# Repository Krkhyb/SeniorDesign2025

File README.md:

**SPE3D Humidity Sensor Repository**

This repository is for a senior design project for University of Science and Technology. Utilizing a HS3003, Rassberry Pi 5, and an LCD we are gathering humidity data on a SPEE3D machine on campus, recording data in a database, and allowing users to output specific data to a csv file for easy export.

Files included here: Gerber of both main PCB and sensor PCB, and schematics.

**Contributers:**

Evan Newcorn - Mechanical Design and PCB Design

Nathan Schoenberg - Housing and Software Implementation

Johnny Leech - Mechanical Design and Reporting

Kyle Kruel - Software Developer and Implementation

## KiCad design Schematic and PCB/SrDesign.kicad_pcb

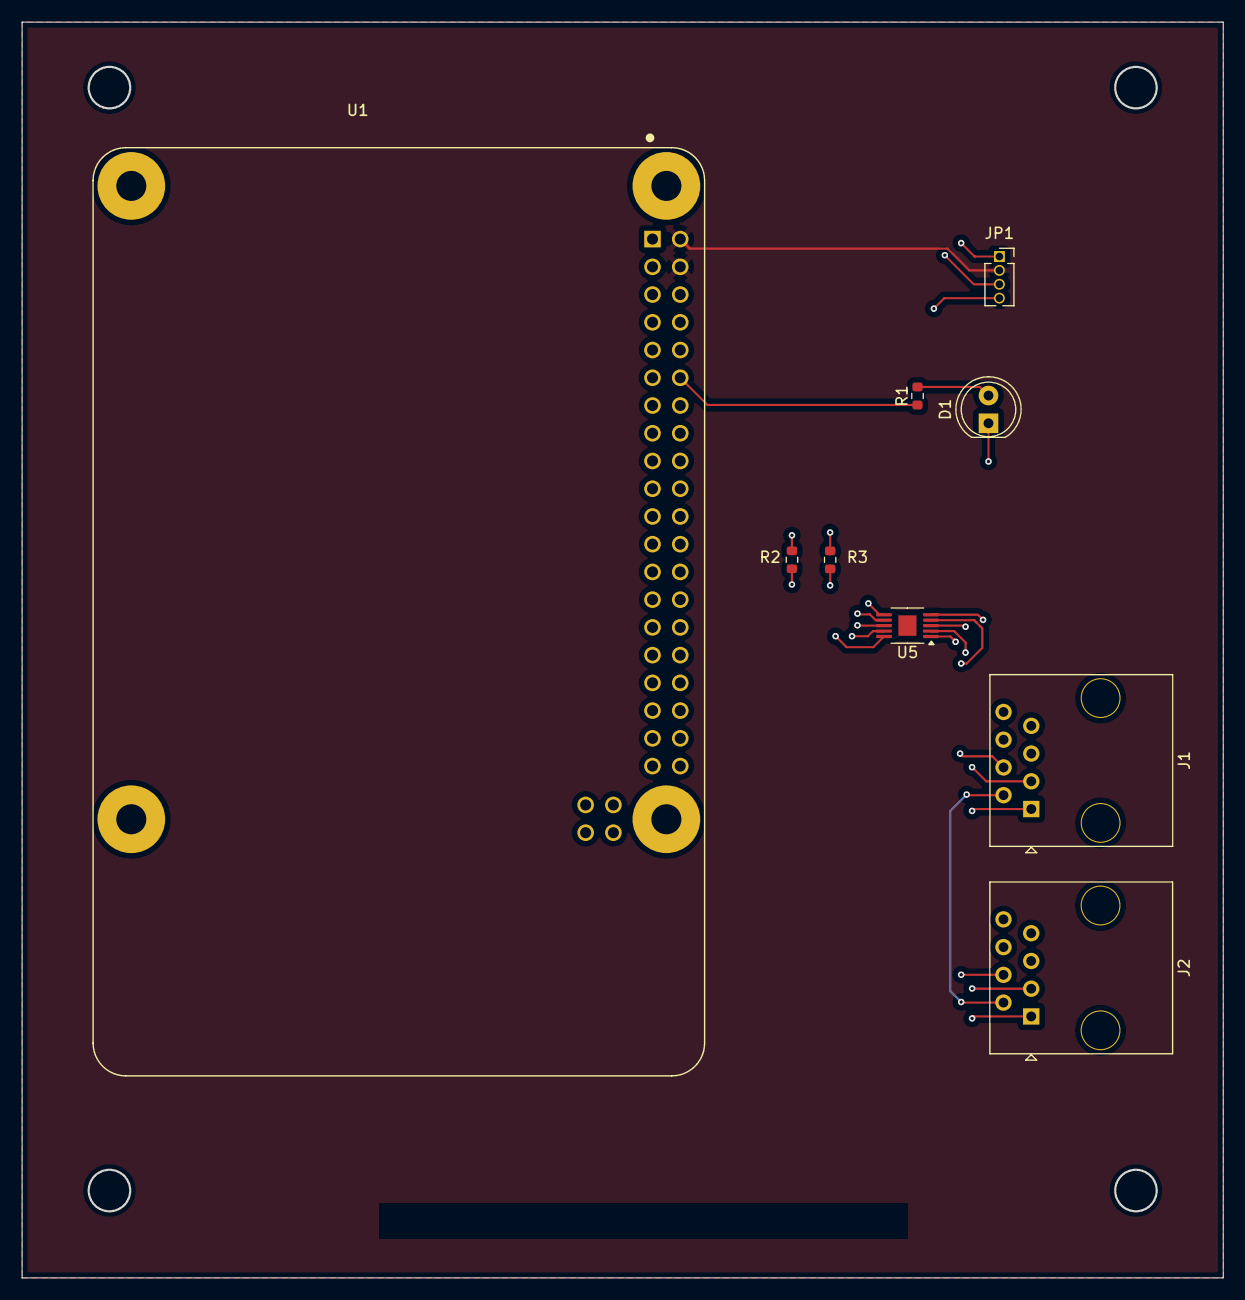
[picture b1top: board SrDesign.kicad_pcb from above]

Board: 4 copper layers, 109.9 x 114.9 mm, 9 parts (0 on the bottom side), 8 nets.

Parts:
D1: LED; LED_D5.0mm
J1, J2: RJ45; RJ45_OST_PJ012-8P8CX_Vertical
JP1: LCD1602; PinSocket_1x04_P1.27mm_Vertical
R1: 100; R_0603_1608Metric
R2, R3: 4.7k; R_0603_1608Metric
U1: RASPBERRY_PI_5_4GB; MODULE_RASPBERRY_PI_4B_4GB
U5: ADS1115; MSOP-10-1EP_3x3mm_P0.5mm_EP1.68x1.88mm

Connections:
/3.3V: J1.1, J2.1, R2.2, R3.2, U1.1 (3V3), U1.17 (3V3), U5.1, U5.8
/5V: JP1.2, U1.2 (5V), U1.4 (5V)
/RDY: U1.11 (GPIO17/GPIO_GEN0), U5.2
/SCL: J1.4, J2.4, JP1.4, R2.1, U1.5 (GPIO3/SCL1), U5.4, U5.6, U5.10
/SDA: J1.3, J2.3, JP1.3, R3.1, U1.3 (GPIO2/SDA1), U5.5, U5.7, U5.9
GND: D1.1 (K), J1.2, J2.2, JP1.1, U1.6 (GND), U1.9 (GND), U1.14 (GND), U1.20 (GND), U1.25 (GND), U1.30 (GND), U1.34 (GND), U1.39 (GND), U5.3
unnamed: D1.2 (A), R1.2
unnamed: R1.1, U1.12 (GPIO18/GPIO_GEN1)

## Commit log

2025-12-12 Adding source code and service routine
2025-12-12 Adding IP Addr Identifier
